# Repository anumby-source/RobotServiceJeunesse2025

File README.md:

# RobotServiceJeunesse2025
Développements pour la séance Service Jeunesse au printemps 2025

# Structure pour le R&D
* Chaque développeur se voit attribué un espace à son nom pour ses propres développements de R&D
* Données pour le véhicule du service jeunesse 2025

Ultérieurement, lorsque l'on aura sélectionné les choix de design et de technologie, on assemblera les développements communs

# Utilisation de Fusion 360 pour l'impression 3D

On peut démarrer cette série de tuto Youtube en mode "très débutant". Un peu lent mais clair. 1, 2, 3, 4, ...

* [Fusion 360 Complet Débutant](https://www.youtube.com/watch?v=3kL6a9yyus8&list=PL0qHSH9_1qY5kvUzO7SlggBShYAllfP7j&index=4)
* [Modélisation une Loupe en français](https://www.youtube.com/watch?v=21fNvLuIeyk&list=PL0qHSH9_1qY5kvUzO7SlggBShYAllfP7j&index=1)
* [Modélisation d'une attache type GoPro](https://www.youtube.com/watch?v=NfXD1W5tZaM&list=PL0qHSH9_1qY5kvUzO7SlggBShYAllfP7j&index=2)
* [Croquis, Contraintes, Dimensions](https://www.youtube.com/watch?v=1mFSI_tEmsY&list=PL0qHSH9_1qY5kvUzO7SlggBShYAllfP7j&index=3)
* [Tournevis à Embout - Régle d'Or, Volumes et Composants](https://www.youtube.com/watch?v=3kL6a9yyus8&list=PL0qHSH9_1qY5kvUzO7SlggBShYAllfP7j&index=4)
* [Bielle et Piston: Jointure, Articulations, Mouvements.](https://www.youtube.com/watch?v=oicK9lwJ6bA&list=PL0qHSH9_1qY5kvUzO7SlggBShYAllfP7j&index=5)
* [Organisation d'un projet et Régle d'Or](https://www.youtube.com/watch?v=NAn41hFw8Yg&list=PL0qHSH9_1qY5kvUzO7SlggBShYAllfP7j&index=6)
* [Tolérances, Historique, Colorisation](https://www.youtube.com/watch?v=N-1HDvVJG_U&list=PL0qHSH9_1qY5kvUzO7SlggBShYAllfP7j&index=7)
* [Survol des "Ateliers"](https://www.youtube.com/watch?v=0DFtvFfrYvw&list=PL0qHSH9_1qY5kvUzO7SlggBShYAllfP7j&index=8)
* [Loft et Sweep](https://www.youtube.com/watch?v=eku9RZ19Kuo&list=PL0qHSH9_1qY5kvUzO7SlggBShYAllfP7j&index=9)
* [Construction Coque de Bateau - Etape 1](https://www.youtube.com/watch?v=NDEB2YS3qxY&list=PL0qHSH9_1qY5kvUzO7SlggBShYAllfP7j&index=10)
* [Construction Coque de Bateau Etape 2](https://www.youtube.com/watch?v=uyDRabeoyRY&list=PL0qHSH9_1qY5kvUzO7SlggBShYAllfP7j&index=11)
* [Extensions (add-ins) et Scripts](https://www.youtube.com/watch?v=a0wj_iS4hvU&list=PL0qHSH9_1qY5kvUzO7SlggBShYAllfP7j&index=12)
* [Coque Minute avec Patch](https://www.youtube.com/watch?v=YINleWgpdjY&list=PL0qHSH9_1qY5kvUzO7SlggBShYAllfP7j&index=13)
* [Apprendre en faisant n'importe quoi!](https://www.youtube.com/watch?v=OFpFc8LrxU4&list=PL0qHSH9_1qY5kvUzO7SlggBShYAllfP7j&index=14)
* [Organisation, Composants, Bodies, Ensembles](https://www.youtube.com/watch?v=pDECKXFHmOQ&list=PL0qHSH9_1qY5kvUzO7SlggBShYAllfP7j&index=15)
* [Conception paramétrique sans paramètres (Où pas?)](https://www.youtube.com/watch?v=bImEM7l9Zes&list=PL0qHSH9_1qY5kvUzO7SlggBShYAllfP7j&index=16)
* [Nouvelle Interface? Pas de panique!](https://www.youtube.com/watch?v=ow5COcHA7XY&list=PL0qHSH9_1qY5kvUzO7SlggBShYAllfP7j&index=17)
* [Réconcilier (Enfin!) les Meshes avec Fusion 360](https://www.youtube.com/watch?v=rIGUrBB8rrw&list=PL0qHSH9_1qY5kvUzO7SlggBShYAllfP7j&index=18)
* [Vous allez aimer les contraintes (dans Fusion 360)](https://www.youtube.com/watch?v=fWU2rNBqDFI&list=PL0qHSH9_1qY5kvUzO7SlggBShYAllfP7j&index=19)
* [Super Mercis !!!!](https://www.youtube.com/watch?v=ioGxxQVQzVY&list=PL0qHSH9_1qY5kvUzO7SlggBShYAllfP7j&index=20)

Autre série pour Fusion 360 (2 séries: débutants, confirmés)

* [TUTORIELS FUSION 360](https://www.youtube.com/channel/UC1f3yfI3YFzhuoScarGSKwA)

TinkerCAD

* [TinkerCAD](https://www.youtube.com/watch?v=egNBQ0hXe2o)
* [TinkerCAD2](https://www.youtube.com/watch?v=DtlmVaoMNMc)

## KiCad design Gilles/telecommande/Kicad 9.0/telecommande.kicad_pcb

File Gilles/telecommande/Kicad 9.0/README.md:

###  Fichiers Kicad pour le PCB de la télécommande

Contient entre autres des symboles et empreintes spécifiques au PCB de la télécommande (suppression des broches non utilisées 

de l'ESP32-C3_mini, diode neopixel à 3 broches)

<p align="center"> 
  
<p/>

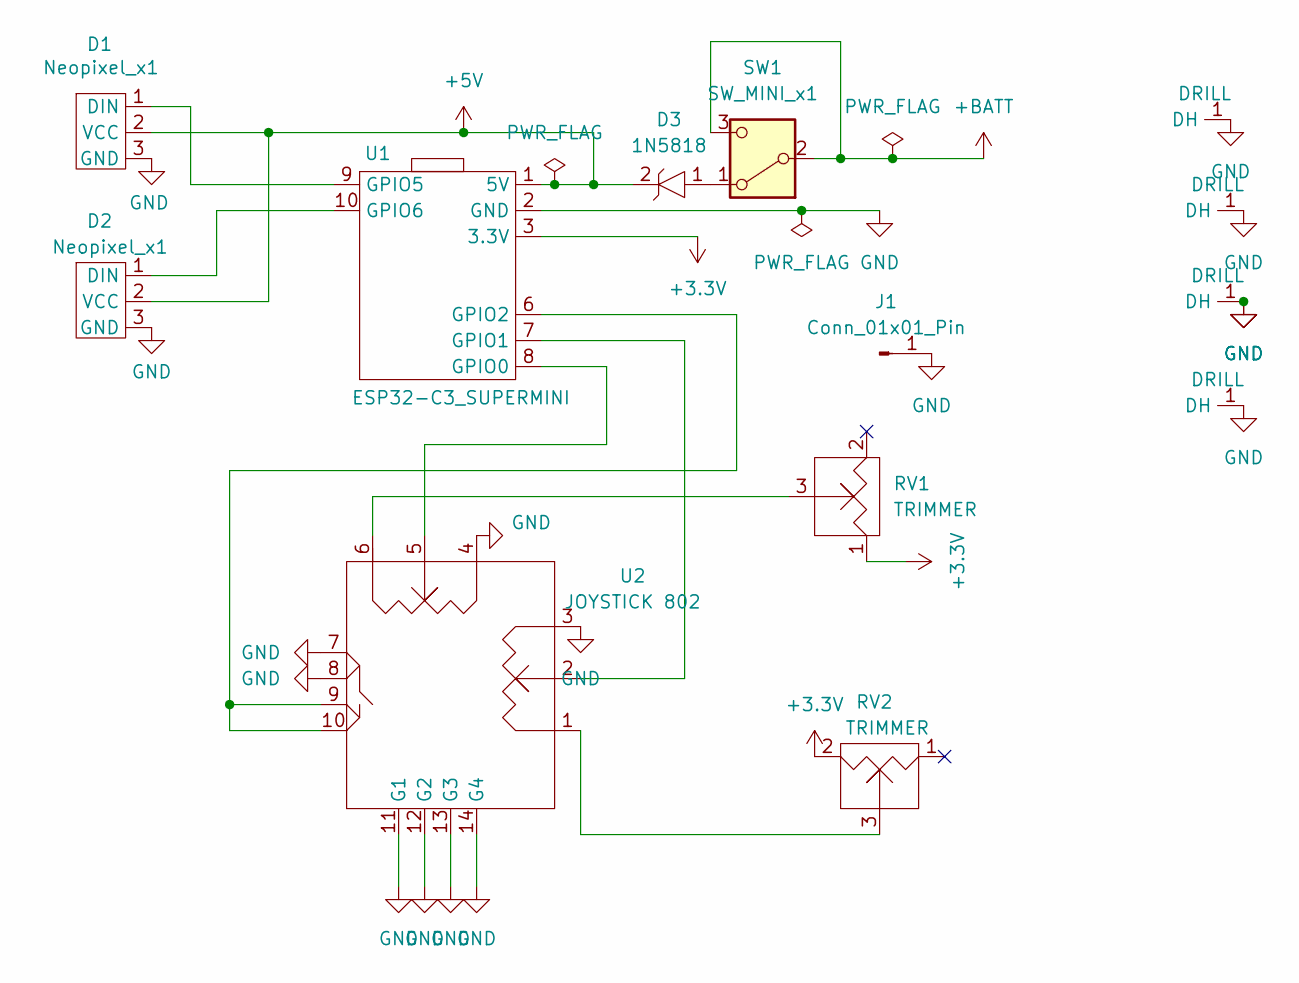
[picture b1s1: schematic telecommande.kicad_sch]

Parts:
D1, D2: Neopixel_x1
D3: 1N5818
DH1, DH2, DH3, DH4: DRILL; DRILL_HOLE
J1: Conn_01x01_Pin; SINGLE PIN
RV1, RV2: TRIMMER
SW1: SW_MINI_x1; SW_MINI_X1
U1: ESP32-C3_SUPERMINI
U2: JOYSTICK 802; JOYSTICK_MODEL_802

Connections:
+3.3V: RV1.1, RV2.2, U1.3 (3.3V)
+5V: D1.2 (VCC), D2.2 (VCC), D3.2, U1.1 (5V)
+BATT: SW1.2 (B), SW1.3 (C)
GND: D1.3 (GND), D2.3 (GND), DH1.1 (DH), DH2.1 (DH), DH3.1 (DH), DH4.1 (DH), J1.1, U1.2 (GND), U2.3, U2.4, U2.7, U2.8, U2.11 (G1), U2.12 (G2), U2.13 (G3), U2.14 (G4)
unnamed: D1.1 (DIN), U1.9 (GPIO5)
unnamed: D2.1 (DIN), U1.10 (GPIO6)
unnamed: RV1.3, U2.6
unnamed: RV2.3, U2.1
unnamed: D3.1, SW1.1 (A)
unnamed: U1.8 (GPIO0), U2.5
unnamed: U1.7 (GPIO1), U2.2
unnamed: U1.6 (GPIO2), U2.9, U2.10

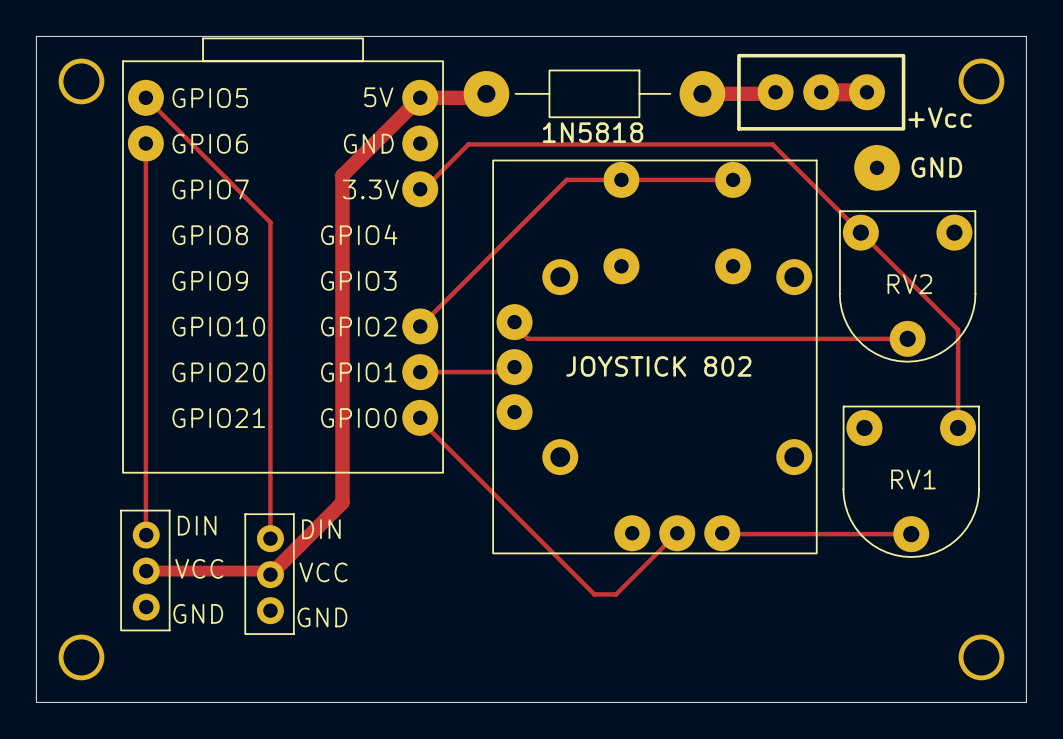
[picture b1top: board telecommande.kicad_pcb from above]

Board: 2 copper layers, 55.0 x 37.0 mm, 13 parts (0 on the bottom side), 12 nets.

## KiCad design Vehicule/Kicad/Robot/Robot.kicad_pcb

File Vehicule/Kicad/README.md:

# On a installé Kicad v8

Puis on ajoute la librairie expressif qui fournit entre autres, les composants Kicad associés au ESP32-C3

https://github.com/espressif/kicad-libraries/tree/legacy_kicad7

La librairie est donc le fichier zip  espressif-kicad-addon.zip

Il faut utiliser l'outil "Gestionnaire de pluin et de contenu" qui va directement installer la librairie expressif à partir du fichier zib précédemment téléchargé

J'ai ajouté dans la librairie "Expressif" les composants nécessaires pour "esp32-c3-supermini" qui n'existaient pas dans la librairie de base

https://github.com/SurrealityLabs/esp32c3-wled

Mise à jour de la librairie (installée dans le commit)

"expressif-kicad-addon.zip"

# Nos développements pour le projet RobotJeunesse

Lors des développements effectués dans le cadre du Robot, j'ai été amenée à créer plusieurs éléments Kicad:
- des symboles,
- des empreintes associées

Ces éléments sont installés dans deux librairies:

1) https://github.com/anumby-source/RobotServiceJeunesse2025/blob/main/Vehicule/Kicad/Anumby.kicad_sym
2) https://github.com/anumby-source/RobotServiceJeunesse2025/tree/main/Vehicule/Kicad/Empreintes.pretty

Si vous souhaitez utiliser Kicad, pour développer dans le cadre de nos projets actuels, vous devrez importer ces librairies dans votre version de Kicad, ainsi les deux projets en cours seront modifiables:

1) https://github.com/anumby-source/RobotServiceJeunesse2025/tree/main/Vehicule/Kicad/T%C3%A9l%C3%A9commande
2) https://github.com/anumby-source/RobotServiceJeunesse2025/tree/main/Vehicule/Kicad/Robot

[Outil 3D](https://circuitcellar.com/research-design-hub/basics-of-design/create-3d-models-of-components-and-board-outlines-in-kicad/)

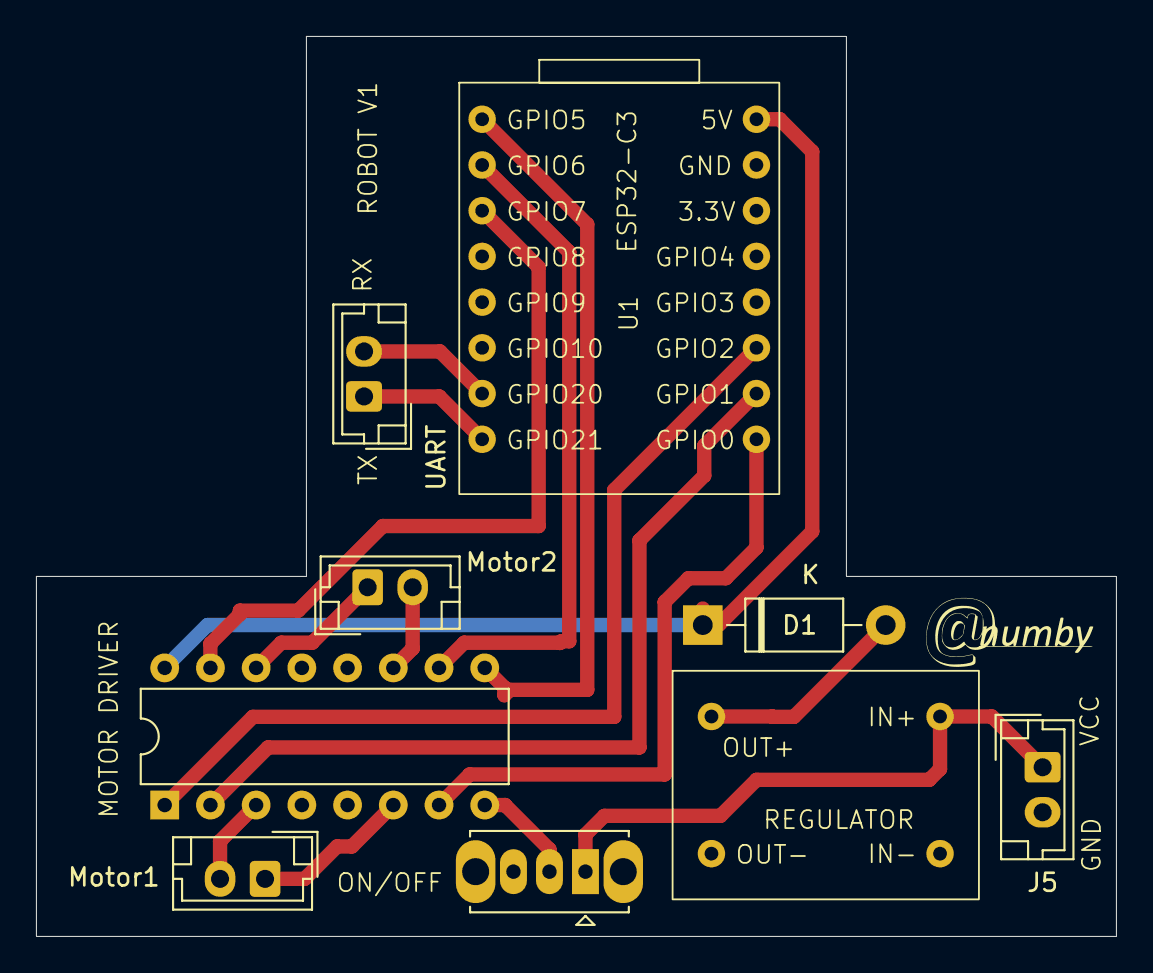
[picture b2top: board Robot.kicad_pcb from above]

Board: 2 copper layers, 60.0 x 50.0 mm, 10 parts (0 on the bottom side), 17 nets.

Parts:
D1: 1N5818; D_DO-41_SOD81_P10.16mm_Horizontal
G: Val**; Logo_Anumby_10
J5: Conn_01x02_Socket_H; JST_EH_B2B-EH-A_1x02_P2.50mm_Vertical
Motor1, Motor2: Conn_01x02_Socket_H; JST_EH_B2B-EH-A_1x02_P2.50mm_Vertical
SW1: SW_DPDT_x2; SW_Slide_SPDT_Straight_CK_OS102011MS2Q
U1: ESP32-C3_SUPERMINI
U2: L293D; DIP-16_W7.62mm
U4: REG_5V; REG_5V_DFR
UART: Conn_01x02_Socket_H; JST_EH_B2B-EH-A_1x02_P2.50mm_Vertical

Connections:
GND: J5.2, U1.2 (GND), U2.4 (GND), U2.5 (GND), U4.2 (GND), U4.4 (GND)
unnamed: D1.2 (A), U4.3 (+VOUT)
unnamed: D1.1 (K), U1.1 (5V), U2.16 (VCC1)
unnamed: U1.9 (GPIO21), UART.1
unnamed: U1.10 (GPIO20), UART.2
unnamed: Motor2.1, U2.14 (4Y)
unnamed: Motor2.2, U2.11 (3Y)
unnamed: Motor1.1, U2.6 (2Y)
unnamed: Motor1.2, U2.3 (1Y)
unnamed: J5.1, SW1.1 (A), U4.1 (+VIN)
unnamed: SW1.2 (B), U2.8 (VCC2)
unnamed: U1.8 (GPIO0), U2.7 (2A)
unnamed: U1.7 (GPIO1), U2.2 (1A)
unnamed: U1.6 (GPIO2), U2.1 (EN1,2)
unnamed: U1.16 (GPIO5), U2.9 (EN3,4)
unnamed: U1.15 (GPIO6), U2.10 (3A)
unnamed: U1.14 (GPIO7), U2.15 (4A)

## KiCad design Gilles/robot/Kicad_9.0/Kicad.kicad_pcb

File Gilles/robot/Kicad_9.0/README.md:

###  Fichiers Kicad pour le PCB du robot

Contient entre autres des symboles et empreintes spécifiques au PCB du robot (suppression des broches non utilisées 

de l'ESP32-C3_mini)

<p align="center"> 
  
<p/>

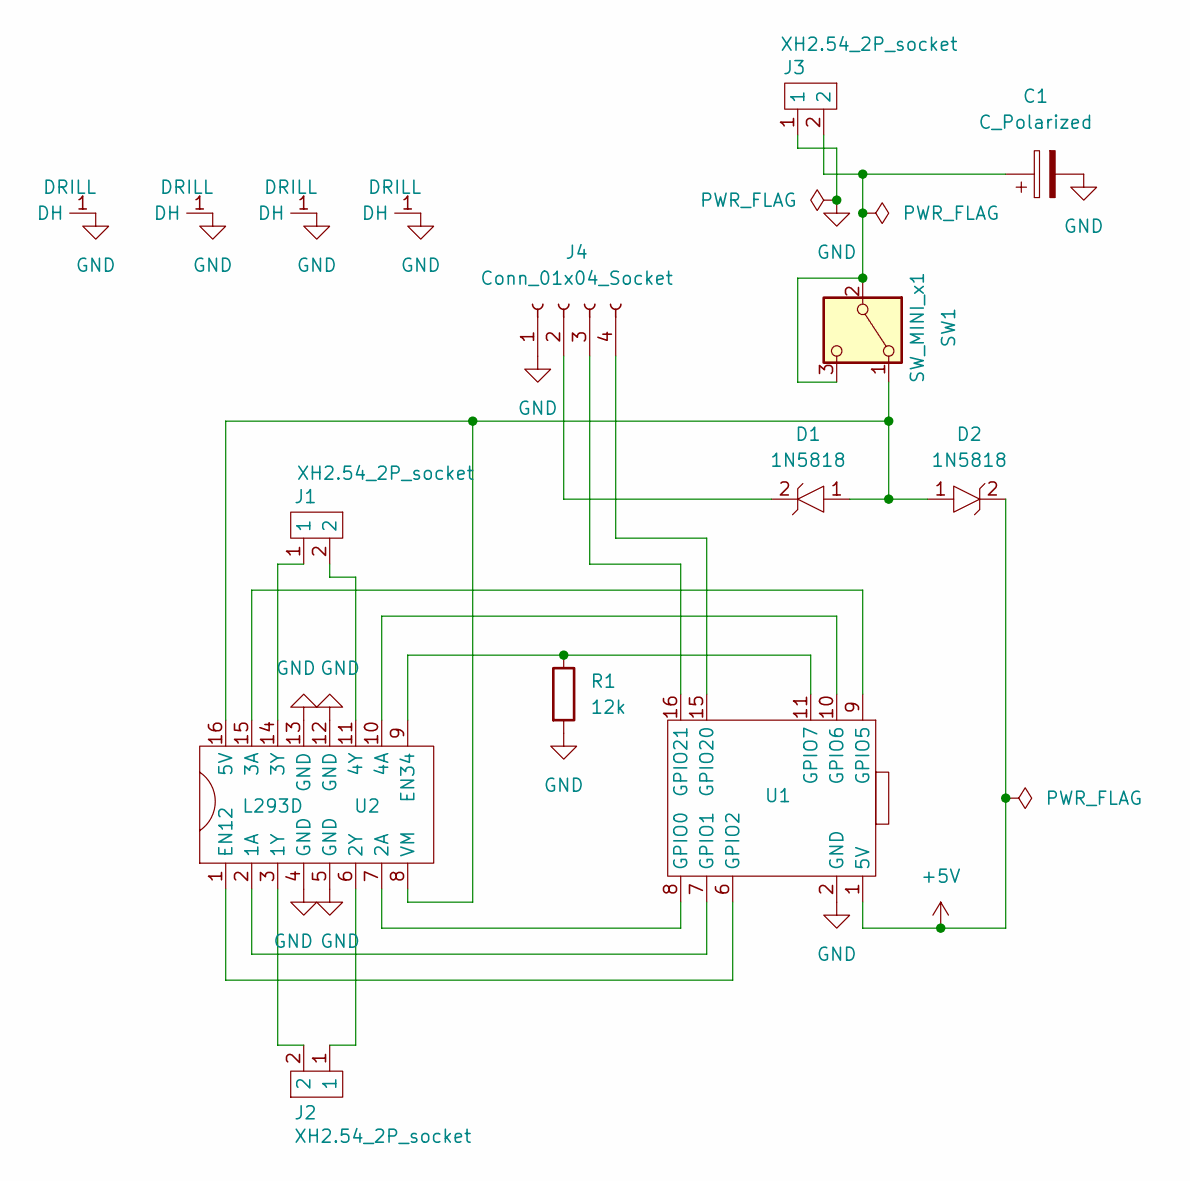
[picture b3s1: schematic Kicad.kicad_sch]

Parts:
C1: C_Polarized; CP_8mm_3.5mm
D1, D2: 1N5818
DH1, DH2, DH3, DH4: DRILL; DRILL_HOLE
J1, J2, J3: XH2.54_2P_socket; XH2.54_2P_soc
J4: Conn_01x04_Socket; NS-Tech_Grove_1x04_P2mm_Vertical
R1: 12k; 1N5818
SW1: SW_MINI_x1; SW_MINI_X1
U1: ESP32-C3_SUPERMINI
U2: L293D

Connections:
+5V: D2.2, U1.1 (5V)
GND: C1.2, DH1.1 (DH), DH2.1 (DH), DH3.1 (DH), DH4.1 (DH), J3.1, J4.1, R1.2, U1.2 (GND), U2.4 (GND), U2.5 (GND), U2.12 (GND), U2.13 (GND)
unnamed: D1.2, J4.2
unnamed: J4.3, U1.16 (GPIO21)
unnamed: J4.4, U1.15 (GPIO20)
unnamed: D1.1, D2.1, SW1.1 (A), U2.8 (VM), U2.16 (5V)
unnamed: C1.1, J3.2, SW1.2 (B), SW1.3 (C)
unnamed: U1.8 (GPIO0), U2.7 (2A)
unnamed: U1.7 (GPIO1), U2.2 (1A)
unnamed: U1.6 (GPIO2), U2.1 (EN12)
unnamed: U1.9 (GPIO5), U2.15 (3A)
unnamed: U1.10 (GPIO6), U2.10 (4A)
unnamed: R1.1, U1.11 (GPIO7), U2.9 (EN34)
unnamed: J2.2, U2.3 (1Y)
unnamed: J2.1, U2.6 (2Y)
unnamed: J1.1, U2.14 (3Y)
unnamed: J1.2, U2.11 (4Y)

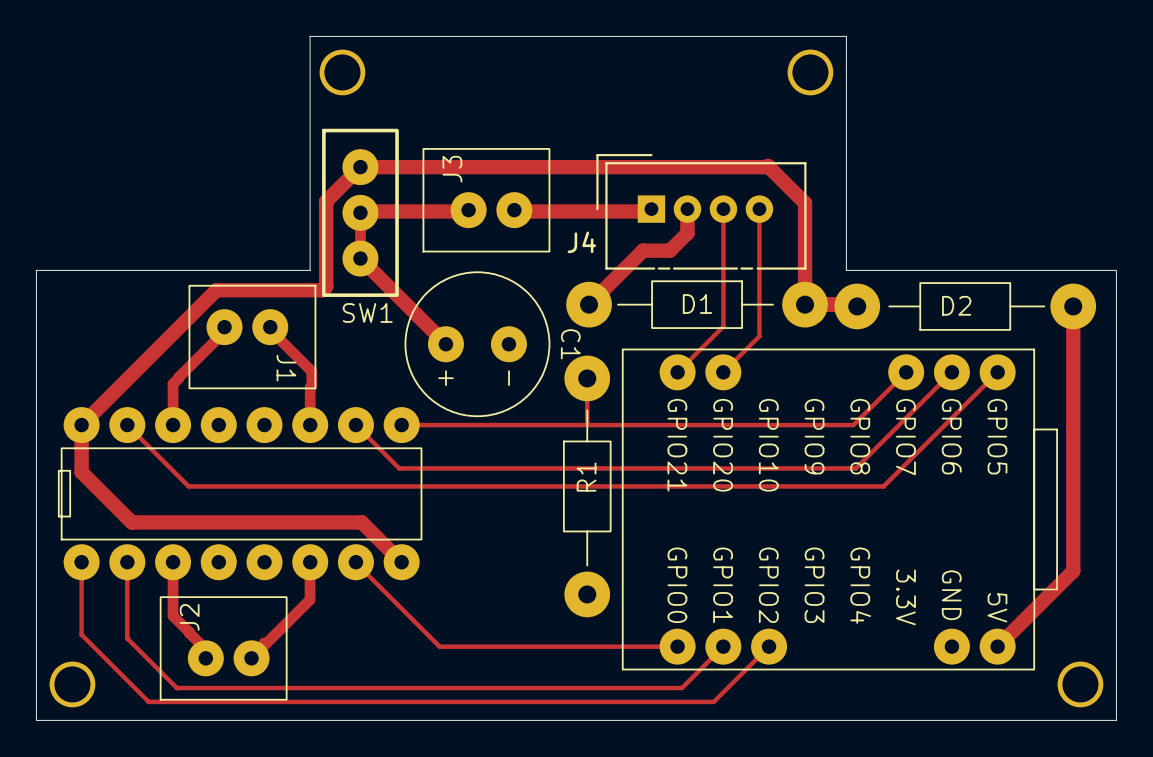
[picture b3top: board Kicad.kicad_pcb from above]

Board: 2 copper layers, 60.0 x 38.0 mm, 15 parts (0 on the bottom side), 17 nets.

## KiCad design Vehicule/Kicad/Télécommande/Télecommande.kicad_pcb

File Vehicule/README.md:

# Dossiers pour les développements Electroniques pour le véhicule

* **Kicad** contient tous les développements électroniques
* plusieurs dossiers contiennent des documentations utilisées lors de la définition des éléments Kicad
  * **ESP32-C3**
  * **Joystick**
  * **Régulateur-DFR0569**

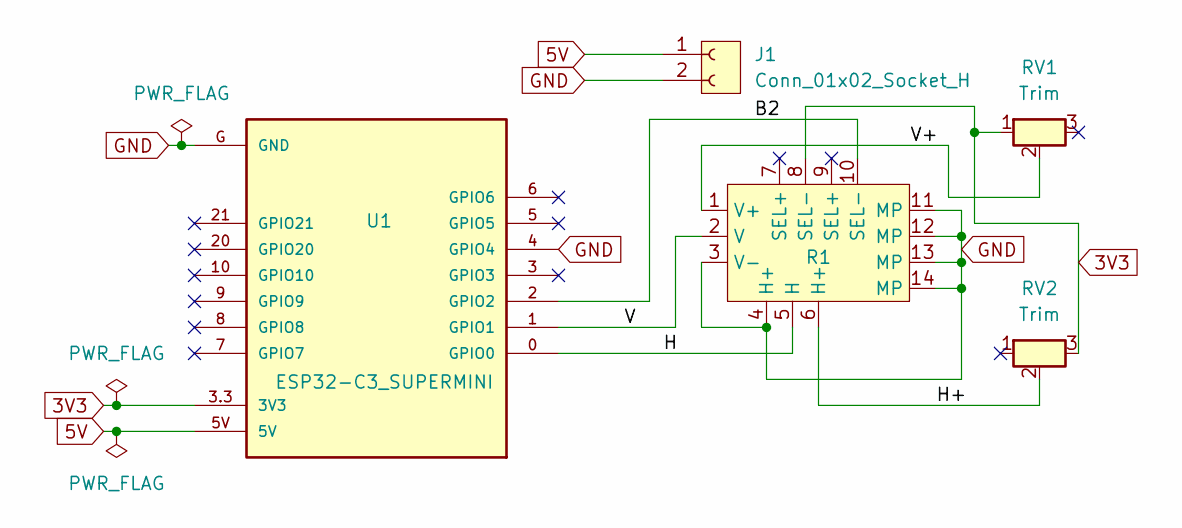
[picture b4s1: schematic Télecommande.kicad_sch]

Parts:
J1: Conn_01x02_Socket_H; JST_PH_S2B-PH-K_1x02_P2.00mm_Horizontal
R1: JOYSTICK_MODEL_802
RV1, RV2: Trim; Potentiometer_Runtron_RM-065_Vertical
U1: ESP32-C3_SUPERMINI; ESP32-C3-SUPERMINI

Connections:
3V3: R1.8 (SEL-), RV1.1, RV2.3, U1.3.3 (3V3)
5V: J1.1, U1.5V
/B2: R1.10 (SEL-), U1.2 (GPIO2)
/H: R1.5 (H), U1.0 (GPIO0)
/H+: R1.6 (H+), RV2.2
/V: R1.2 (V), U1.1 (GPIO1)
/V+: R1.1 (V+), RV1.2
GND: J1.2, R1.3 (V-), R1.4 (H+), R1.11 (MP), R1.12 (MP), R1.13 (MP), R1.14 (MP), U1.4 (GPIO4), U1.G (GND)

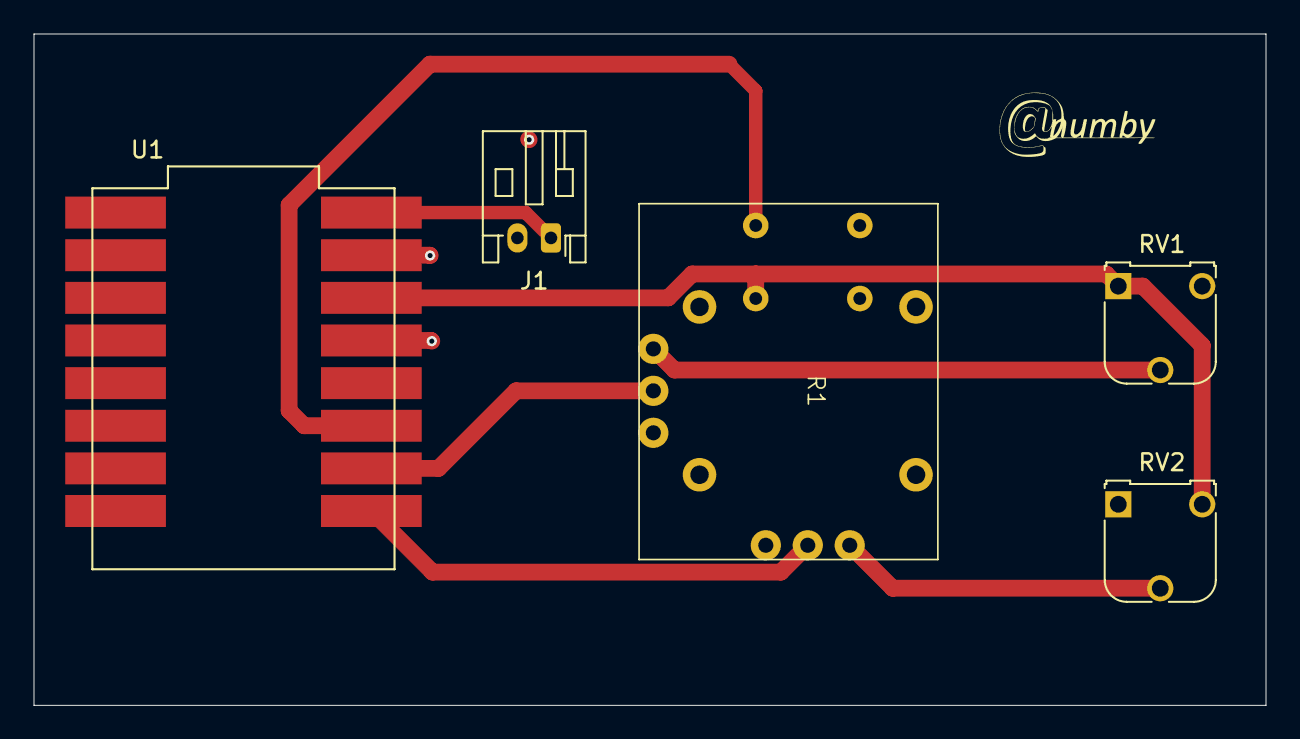
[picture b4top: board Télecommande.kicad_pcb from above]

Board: 2 copper layers, 73.4 x 40.0 mm, 6 parts (0 on the bottom side), 8 nets.

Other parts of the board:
G: Val**; Logo_Anumby_10

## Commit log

2024-05-28 Mise en place de la structure de développement . En commençant par la structure de R&D
2024-05-29 Petit essai avec Flask
2024-05-30 Petit essai avec JS
2024-05-31 Essais avec JS Préparation pour piloter un robot
2024-06-01 Ajoute une simulation du contrôle du robot
2025-01-29 Ajoute la liste des composants à acheter pour la fabrication du véhicule
2025-01-29 Première version de circuits électroniques pour la télécommande et pour le véhicule (à associer avec la liste BOM)
2025-01-29 Addition des composants pour le ESP32-C3-SUPERMINI. Utilisation de ce module dans le projet Kicad
2025-01-30 Création du joystick Ajout du joystick Ajout des trimmers
2025-02-02 Empeinte du joystick
2025-02-02 Pour le joystick ou récupère les documents au format EAGLE mais on n'arrive pas à les convertir au format KiCad. Donc on transfert manuellement les données de l'empreinte.
2025-02-02 BOM: mise au format MD
2025-02-02 Compléter le schéma
2025-02-05 Suppression des anciennes versions du projet Télécommande
2025-02-06 Un peu de ménage dans les dossiers
2025-02-06 Schema et implantation du circuit pour le robot ajoute un dossier pour le projet Kicad pour la télécommande
2025-02-06 Schema et implantation du circuit pour le robot
2025-02-06 La librairie Kicad Anumby avec les composants ajoutés Cette librairie est associée à la librairie d'empreintes
2025-02-07 Transfert du SUPERMINI (composant et empreintes) dans les librairies locales (Anumby et Empreintes)
2025-02-07 Transfert du SUPERMINI (composant et empreintes) dans les librairies locales (Anumby et Empreintes) Renommer Empreintes -> Anumby
2025-02-10 TAjouter la couche de masse pour la télécommande
2025-02-10 Ajout de la couche de masse pour Robot Ajout d'un connecteur 1 pin Mise à jour de tous les PCB et les Schémas
2025-02-11 Ajout de logo Anumby pour PCB (2 versions)
2025-02-12 Ajout de logo Anumby pour PCB
2025-02-13 Ajout de logo Anumby pour PCB Mise à jour des empreintes, des connecteurs des librairies
2025-02-13 Finalisation du PCB de la Télécommande puis génération des fichiers de fabrication Gerber
2025-02-13 Finalisation du PCB du Robot puis génération des fichiers de fabrication Gerber
2025-02-18 Ajout d'un titre ROBOT / TELECOMMANDE et d'une version (V1) sur la sérigraphie
2025-02-18 Remplacement de l'empreinte ESP32 de surface pour une empreinte traversante
2025-03-18 Modification des fichiers Kicad de Gilles Premier test de la gestion de l'historique du trajet Chris/robot.py
2025-03-18 Simulation du programme robot.py - avec motor - avec détection de ville - 6 villes, trajet jusqu'à la détection de la dernière ville
2025-03-18 Simulation du programme robot.py - avec motor - avec détection de ville - 6 villes, trajet jusqu'à la détection de la dernière ville - impression de l'historique ordonné
2025-03-19 Simulation du programme robot.py - paramètre VILLES = nombre max de villes - implémentation de 2 algorithmes: 1) détection des villes à partir de la ville 1 jusqu'à la ville VILLES mais sans ordre in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
2025-03-19 Rename fixation moteur N20 v3.stl to fixation moteur.stl
2025-04-24 Présentation sur IA
2025-04-24 Présentation sur IA fix from Arnaud
2025-04-25 Présentation sur IA fixes
